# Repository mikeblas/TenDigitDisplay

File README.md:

Here is a project I made in the summer of 2025.

On a driving trip from Chicago back home to Seattle, I discovered [American Science and Surplus](https://sciplus.com/). Their store in Geneva, Illinois has lots of fun stuff, including some two-digit LED displays that I thought I could use to make a neat display.

The circuit in this project multiplexes the displays so they can be driven by the ESP-32. After a few iterations on the breadboard, I got boards done at [OSH Park](https://oshpark.com/) and soldered them up with through-hole parts that I mostly had in my inventory.

The web server on the ESP-32 has two endpoints: one takes a ten-digit hex string, which is a bitmap of the segments to illuminate on the display. The other takes a string of numbers to display -- they're converted from ASCII to their seven-segment representation.

I want to use the project to display some stock prices as they change. Since there's just seven segments, it's a bit crude, but something like "183.78d 1.19" means that the issue I'm tracking is at $183.78 per share, down (for "d") $1.19 per share since the last close.

Right now, all the smarts are in a Python scripts that run on a desktop computer. That script pokes at those endpoints and the ESP-32 just scans the multiplexed displays to show the last thing it was told. Eventually, the device could be standalone, though that comes with a few problems that I'll need to sort out.

Things to do:

* Make the Python script support multiple devices
* Show the DHCP-assigned IP address of the ESP-32 on the LEDs at startup
* Have the ESP-32 beacon a UDP message for automatic discovery by client scripts
* Smarter endpoints: accept characters and decimal points, for example
* Use the on-board LED to indicate stale data -- if no client has made an update in some time

And probably a few more things. But I'm also thinking about 16-segment display with 2 rows of 20 characters for a bit more fidelity ...

This repo contains these directories:

* `assets`: some pictures for the readme
* `TenDigitPCB`: a KiCAD project (including shape and footprint files) for the PCB and its components
* `TenDigitsIDF`: Visual Studio Code project for the ESP-32 IDF to implement the web server and multiplexing
* `TenDigitQuoter`: A Python project (for PyCharm) that shows quotes for a stock from the Yahoo! Finance API

Here are some pictures:

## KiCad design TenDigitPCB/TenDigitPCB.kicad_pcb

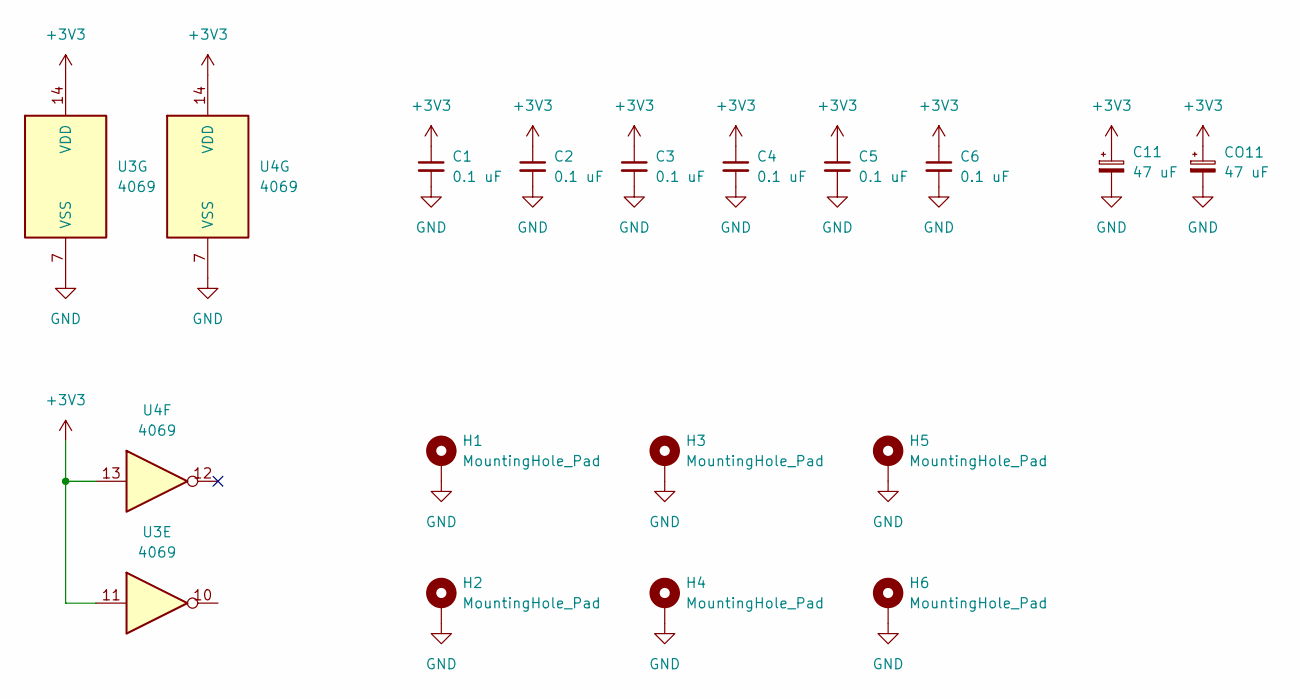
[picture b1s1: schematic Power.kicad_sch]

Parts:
C1, C2, C3, C4, C5, C6: 0.1 uF; C_Disc_D6.0mm_W2.5mm_P5.00mm
C11: 47 uF; CP_Axial_L18.0mm_D8.0mm_P25.00mm_Horizontal
CO11: 47 uF; CP_Radial_D6.3mm_P2.50mm
H1, H2, H3, H4, H5, H6: MountingHole_Pad; MountingHole_3.2mm_M3_Pad_Via
U3, U4: 4069; DIP-14_W7.62mm

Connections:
+3V3: C1.1, C2.1, C3.1, C4.1, C5.1, C6.1, C11.1, CO11.1, U3.11, U3.14 (VDD), U4.13, U4.14 (VDD); also elsewhere on the board
GND: C1.2, C2.2, C3.2, C4.2, C5.2, C6.2, C11.2, CO11.2, H1.1, H2.1, H3.1, H4.1, H5.1, H6.1, U3.7 (VSS), U4.7 (VSS); also elsewhere on the board

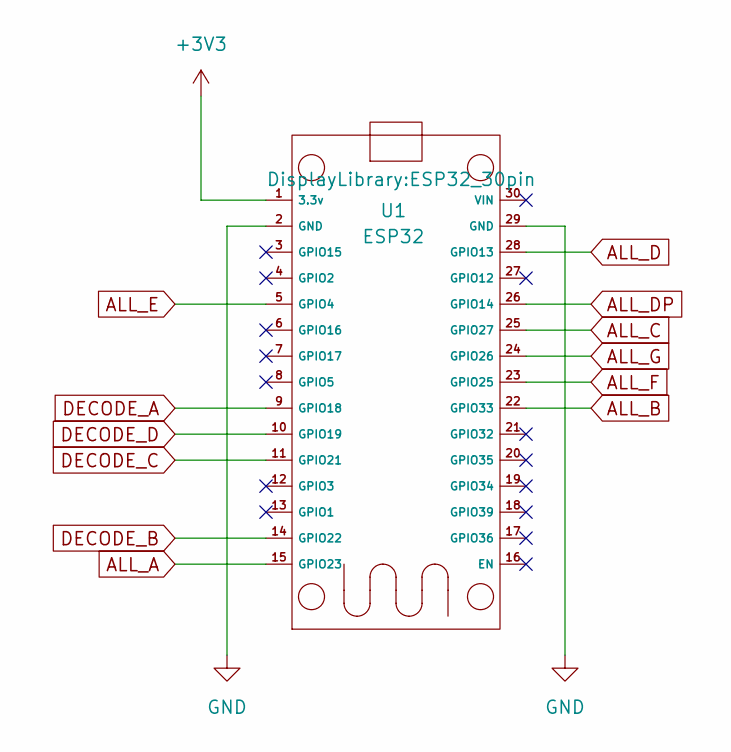
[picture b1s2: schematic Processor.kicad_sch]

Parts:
U1: ESP32; ESP32_30pin

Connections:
+3V3: U1.1 (3.3v); also elsewhere on the board
ALL_A: U1.15 (GPIO23); also elsewhere on the board
ALL_B: U1.22 (GPIO33); also elsewhere on the board
ALL_C: U1.25 (GPIO27); also elsewhere on the board
ALL_D: U1.28 (GPIO13); also elsewhere on the board
ALL_DP: U1.26 (GPIO14); also elsewhere on the board
ALL_E: U1.5 (GPIO4); also elsewhere on the board
ALL_F: U1.23 (GPIO25); also elsewhere on the board
ALL_G: U1.24 (GPIO26); also elsewhere on the board
DECODE_A: U1.9 (GPIO18); also elsewhere on the board
DECODE_B: U1.14 (GPIO22); also elsewhere on the board
DECODE_C: U1.11 (GPIO21); also elsewhere on the board
DECODE_D: U1.10 (GPIO19); also elsewhere on the board
GND: U1.2 (GND), U1.29 (GND); also elsewhere on the board

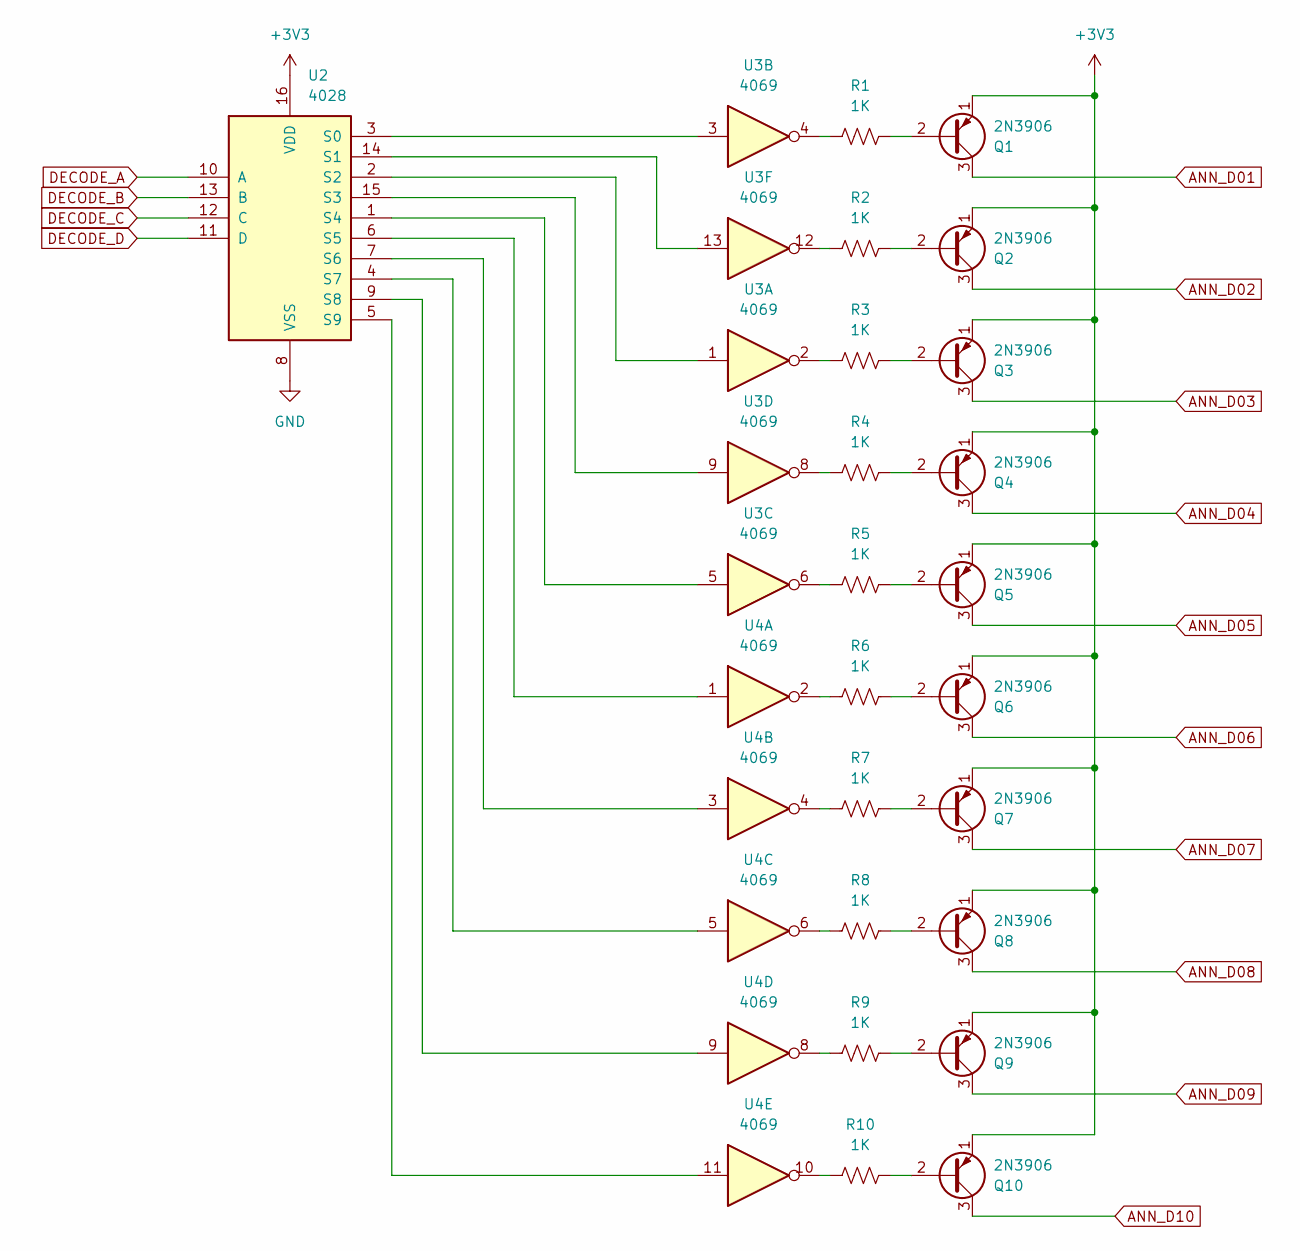
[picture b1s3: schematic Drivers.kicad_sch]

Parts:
Q1, Q2, Q3, Q4, Q5, Q6, Q7, Q8, Q9, Q10: 2N3906; TO-92_Inline
R1, R2, R3, R4, R5, R6, R7, R8, R9, R10: 1K; R_Axial_DIN0207_L6.3mm_D2.5mm_P10.16mm_Horizontal
U2: 4028; DIP-16_W7.62mm
U3, U4: 4069; DIP-14_W7.62mm

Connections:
+3V3: Q1.1 (E), Q2.1 (E), Q3.1 (E), Q4.1 (E), Q5.1 (E), Q6.1 (E), Q7.1 (E), Q8.1 (E), Q9.1 (E), Q10.1 (E), U2.16 (VDD); also elsewhere on the board
ANN_D01: Q1.3 (C); also elsewhere on the board
ANN_D02: Q2.3 (C); also elsewhere on the board
ANN_D03: Q3.3 (C); also elsewhere on the board
ANN_D04: Q4.3 (C); also elsewhere on the board
ANN_D05: Q5.3 (C); also elsewhere on the board
ANN_D06: Q6.3 (C); also elsewhere on the board
ANN_D07: Q7.3 (C); also elsewhere on the board
ANN_D08: Q8.3 (C); also elsewhere on the board
ANN_D09: Q9.3 (C); also elsewhere on the board
ANN_D10: Q10.3 (C); also elsewhere on the board
DECODE_A: U2.10 (A); also elsewhere on the board
DECODE_B: U2.13 (B); also elsewhere on the board
DECODE_C: U2.12 (C); also elsewhere on the board
DECODE_D: U2.11 (D); also elsewhere on the board
GND: U2.8 (VSS); also elsewhere on the board
unnamed: Q1.2 (B), R1.2
unnamed: Q2.2 (B), R2.2
unnamed: Q3.2 (B), R3.2
unnamed: Q4.2 (B), R4.2
unnamed: Q5.2 (B), R5.2
unnamed: Q6.2 (B), R6.2
unnamed: Q7.2 (B), R7.2
unnamed: Q8.2 (B), R8.2
unnamed: Q9.2 (B), R9.2
unnamed: Q10.2 (B), R10.2
unnamed: R1.1, U3.4
unnamed: R2.1, U3.12
unnamed: R3.1, U3.2
unnamed: R4.1, U3.8
unnamed: R5.1, U3.6
unnamed: R6.1, U4.2
unnamed: R7.1, U4.4
unnamed: R8.1, U4.6
unnamed: R9.1, U4.8
unnamed: R10.1, U4.10
unnamed: U2.3 (S0), U3.3
unnamed: U2.14 (S1), U3.13
unnamed: U2.2 (S2), U3.1
unnamed: U2.15 (S3), U3.9
unnamed: U2.1 (S4), U3.5
unnamed: U2.6 (S5), U4.1
unnamed: U2.7 (S6), U4.3
unnamed: U2.4 (S7), U4.5
unnamed: U2.9 (S8), U4.9
unnamed: U2.5 (S9), U4.11

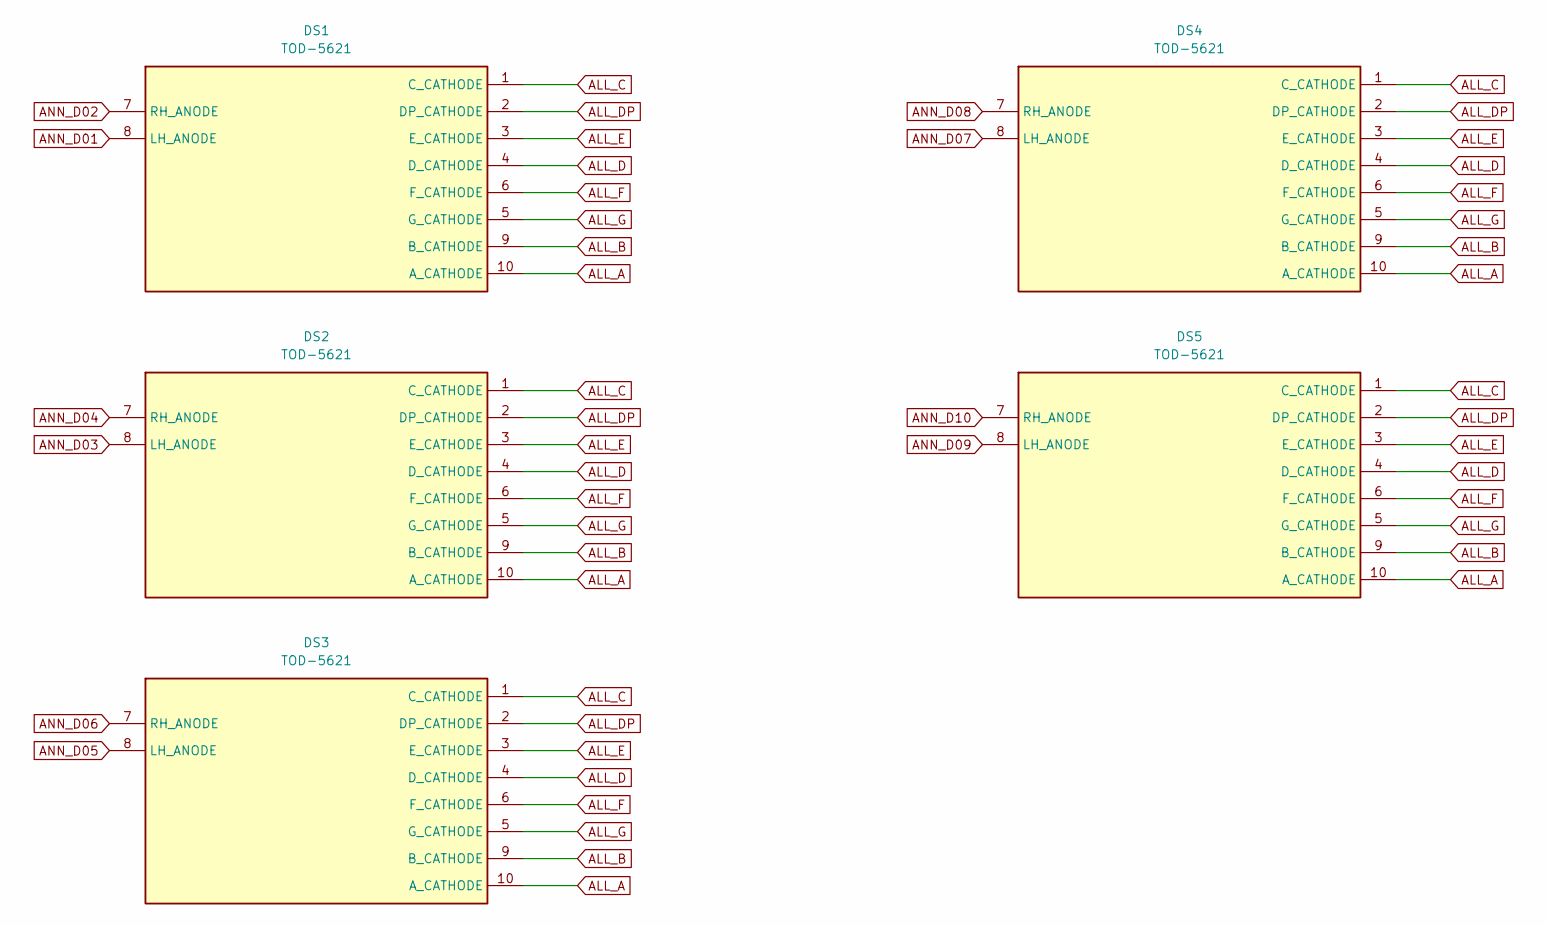
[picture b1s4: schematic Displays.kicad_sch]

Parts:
DS1, DS2, DS3, DS4, DS5: TOD-5621; Mouser Part Number 630-HDSP-K511

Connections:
ALL_A: DS1.10 (A_CATHODE), DS2.10 (A_CATHODE), DS3.10 (A_CATHODE), DS4.10 (A_CATHODE), DS5.10 (A_CATHODE); also elsewhere on the board
ALL_B: DS1.9 (B_CATHODE), DS2.9 (B_CATHODE), DS3.9 (B_CATHODE), DS4.9 (B_CATHODE), DS5.9 (B_CATHODE); also elsewhere on the board
ALL_C: DS1.1 (C_CATHODE), DS2.1 (C_CATHODE), DS3.1 (C_CATHODE), DS4.1 (C_CATHODE), DS5.1 (C_CATHODE); also elsewhere on the board
ALL_D: DS1.4 (D_CATHODE), DS2.4 (D_CATHODE), DS3.4 (D_CATHODE), DS4.4 (D_CATHODE), DS5.4 (D_CATHODE); also elsewhere on the board
ALL_DP: DS1.2 (DP_CATHODE), DS2.2 (DP_CATHODE), DS3.2 (DP_CATHODE), DS4.2 (DP_CATHODE), DS5.2 (DP_CATHODE); also elsewhere on the board
ALL_E: DS1.3 (E_CATHODE), DS2.3 (E_CATHODE), DS3.3 (E_CATHODE), DS4.3 (E_CATHODE), DS5.3 (E_CATHODE); also elsewhere on the board
ALL_F: DS1.6 (F_CATHODE), DS2.6 (F_CATHODE), DS3.6 (F_CATHODE), DS4.6 (F_CATHODE), DS5.6 (F_CATHODE); also elsewhere on the board
ALL_G: DS1.5 (G_CATHODE), DS2.5 (G_CATHODE), DS3.5 (G_CATHODE), DS4.5 (G_CATHODE), DS5.5 (G_CATHODE); also elsewhere on the board
ANN_D01: DS1.8 (LH_ANODE); also elsewhere on the board
ANN_D02: DS1.7 (RH_ANODE); also elsewhere on the board
ANN_D03: DS2.8 (LH_ANODE); also elsewhere on the board
ANN_D04: DS2.7 (RH_ANODE); also elsewhere on the board
ANN_D05: DS3.8 (LH_ANODE); also elsewhere on the board
ANN_D06: DS3.7 (RH_ANODE); also elsewhere on the board
ANN_D07: DS4.8 (LH_ANODE); also elsewhere on the board
ANN_D08: DS4.7 (RH_ANODE); also elsewhere on the board
ANN_D09: DS5.8 (LH_ANODE); also elsewhere on the board
ANN_D10: DS5.7 (RH_ANODE); also elsewhere on the board

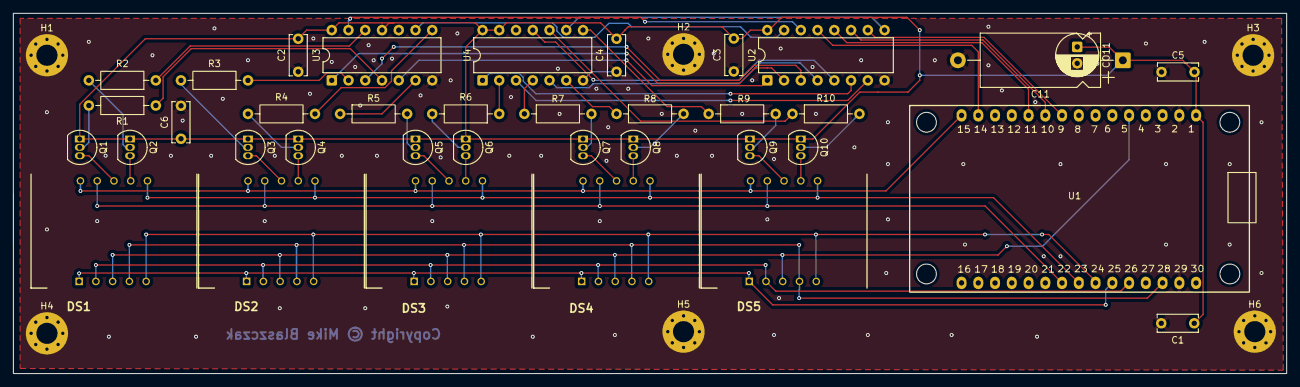
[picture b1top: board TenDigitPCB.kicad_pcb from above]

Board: 2 copper layers, 193.1 x 54.6 mm, 43 parts (0 on the bottom side), 54 nets.

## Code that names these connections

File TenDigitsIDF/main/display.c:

#include "sdkconfig.h"
#include "freertos/FreeRTOS.h"
#include "freertos/task.h"

#include "esp_flash.h"

#include "driver/gpio.h"
#include "hal/gpio_ll.h"


#include "globals.h"



MY_DRAM_ATTR uint8_t dpPlace = 0;

MY_DRAM_ATTR uint64_t counter = 0;
MY_DRAM_ATTR uint8_t counterDigits[10];

// the scanner writes these segments each scan
MY_DRAM_ATTR uint8_t segmentValues[10];


// segments are active low
static const uint8_t SEGMENT_A = 23; // was 32
static const uint8_t SEGMENT_B = 33;
static const uint8_t SEGMENT_C = 27;
static const uint8_t SEGMENT_D = 13;
static const uint8_t SEGMENT_E = 4;
static const uint8_t SEGMENT_F = 25;
static const uint8_t SEGMENT_G = 26;
static const uint8_t SEGMENT_DP = 14;

// these go to CD4028 decoder
static const uint8_t DECODE_A = 18;
static const uint8_t DECODE_B = 22;
static const uint8_t DECODE_C = 21;
static const uint8_t DECODE_D = 19;

#define MY_DRAM_ATTR DRAM_ATTR
// #define MY_DRAM_ATTR 

/* const */ MY_DRAM_ATTR uint8_t digitToSegments[] =
{
    0b00111111,   // digit 0
    0b00000110,   // digit 1
    0b01011011,   // digit 2
    0b01001111,   // digit 3
    0b01100110,   // digit 4
    0b01101101,   // digit 5
    0b01111101,   // digit 6
    0b00000111,   // digit 7
    0b01111111,   // digit 8
    0b01100111,   // digit 9
    0b01110111,   // digit A
    0b01111100,   // digit b
    0b00111001,   // digit C
    0b01011110,   // digit d
    0b01111001,   // digit E
    0b01110001,   // digit F
};

static /* const */ MY_DRAM_ATTR uint8_t segmentMap[] =
{
    SEGMENT_A,
    SEGMENT_B,
    SEGMENT_C,
    SEGMENT_D,
    SEGMENT_E,
    SEGMENT_F,
    SEGMENT_G,
    SEGMENT_DP
};

static /* const */ MY_DRAM_ATTR uint8_t decodeMap[] =
{
    DECODE_A,
    DECODE_B,
    DECODE_C,
    DECODE_D
};

/*
    activate the given common anode on the given digit
    n is [0..9], and 0 is the left-most digit
*/
/* IRAM_ATTR */ void activateDecoderChannel(uint8_t n)
{
#if 0
    gpio_set_level(DECODE_A, (n & 1) == 0 ? LOW : HIGH);
    gpio_set_level(DECODE_B, (n & 2) == 0 ? LOW : HIGH);
    gpio_set_level(DECODE_C, (n & 4) == 0 ? LOW : HIGH);
    gpio_set_level(DECODE_D, (n & 8) == 0 ? LOW : HIGH);
#else

    uint32_t sets = 0;
    uint32_t clears = 0;

    uint8_t mask = 1;
    for (uint8_t i = 0; i < 4; i++, mask <<= 1)
    {
        if ((n & mask) == 0)
            clears |= (uint32_t)1 << decodeMap[i];
        else
            sets |= (uint32_t)1 << decodeMap[i];
        // ESP_LOGI(LOG_TAG, "n = %d, mask = %d, sets = %ld and clears = %ld", i, mask, sets, clears);
    }

    // ESP_LOGI(LOG_TAG, "got %d, sets = %ld and clears = %ld", (int) n, sets, clears);

    GPIO.out_w1ts = sets;
    GPIO.out_w1tc = clears;

#endif
}


/*
    Write the given segment bitmask to the segment output pins, 
    observing active low logic for the common anode part.

    The segments parameter has a bit on for a segment to be lit. 
    Segment A is the LSB, and the DP is the MSB. Bits in the parameter
    are set to turn the corresponding segment on.
*/
/* IRAM_ATTR */ void writeSegments(uint8_t segments)
{
#if 0
    uint8_t mask = 1;
    for (int x = 0; x < 8; x++)
    {
        gpio_set_level(segmentMap[x], ((segments & mask) == 0) ? HIGH : LOW);
        mask <<= 1;
    }
#else
    uint32_t sets = 0;
    uint32_t clears = 0;

    uint32_t sets32 = 0;
    uint32_t clears32 = 0;

    uint8_t mask = 1;
    for (uint8_t i = 0; i < 8; i++, mask <<= 1)
    {
        // note this implements active low: a 1 in the bitmask will clear the GPIO line
        if ((segments & mask) != 0)
        {
            if (segmentMap[i] < 32)
                clears |= (uint32_t)1U << segmentMap[i];
            else
                clears32 |= (uint32_t)1U << (segmentMap[i] - 32);
        }
        else
        {
            if (segmentMap[i] < 32)
                sets |= (uint32_t)1U << segmentMap[i];
            else
                sets32 |= (uint32_t)1U << (segmentMap[i] - 32);
        }
    }

    GPIO.out_w1ts = sets;
    GPIO.out_w1tc = clears;

    GPIO.out1_w1ts.val = sets32;
    GPIO.out1_w1tc.val = clears32;
#endif
}


/*
    turn on the DP in the given digit
*/
void set_decimal_point(uint8_t digit)
{
    segmentValues[digit] |= 0x80;
}


/*
    turn off the DP in the given digit
*/
void clear_decimal_point(uint8_t digit)
{
    segmentValues[digit] &= 0x80;
}


/*
    clear the given GPIO pin, then set it up as an output
*/
static void set_output(gpio_num_t pin)
{
    gpio_reset_pin(pin);
    gpio_set_direction(pin, GPIO_MODE_OUTPUT);
}


/*
    sets up our GPIO pins during initialization
*/
void setup_pins(void)
{
    // all the segments are outputs
    for (int n = 0; n < _countof(segmentMap); n++)
        set_output(segmentMap[n]);

    // built-in is an output
    set_output(LED_BUILTIN);

    // drives are outputs
    set_output(DECODE_A);
    set_output(DECODE_B);
    set_output(DECODE_C);
    set_output(DECODE_D);
}


/*
void setDP(bool on)
{
    gpio_set_level(SEGMENT_DP, on ? LOW : HIGH);
}
*/


void counter_to_segments(void)
{
    for (int n = 0; n < 10; n++)
    {
        segmentValues[n] = digitToSegments[counterDigits[n]];
    }
}

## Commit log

2025-11-30 remove old prototype; make DataSheets folder
2025-12-10 add pictures to README, cleanup *.bak files
2025-12-10 add TenDigitQuoter Python project
2025-12-10 fix markdown
2025-12-10 more readme markdown fixes
2025-12-10 fiddle with README
2025-12-19 display IP address at startup

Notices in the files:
TenDigitPCB/TenDigitPCB.kicad_pcb:
Copyright © Mike Blaszczak
